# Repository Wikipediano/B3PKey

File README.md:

# B3PKey
 This is the first custom keyboard that I have designed.
 It is an ortholinear 75% keyboard which, when completed, will have been entirely designed and built by me.
 
 I have been inspired to do this project by <a href="https://www.reddit.com/user/JustOneMorePixel">u/JustOneMorePixel</a>, and I have gone through ai03's book <a href="https://wiki.ai03.com/books/pcb-design">*PCB Design*</a> and Hadi Iskandarani's YouTube series <a href="https://www.youtube.com/playlist?list=PLbtY7JsOJDYkHNuTmBtGgaWv_qipKeL-u">*PCB Design for Mechanical Keyboards*</a>.

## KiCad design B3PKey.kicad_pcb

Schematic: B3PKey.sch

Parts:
C1, C2: 22pF; C_0805_2012Metric
C3: 1uF; C_0805_2012Metric
C4, C5, C6: 0.1uF; C_0805_2012Metric
C7: 10uF; C_0805_2012Metric
D1, D2, D3, D4, D5, D6, D7, D8, D9, D10, D11, D12, D13, D14, D15, D16, D17, D18, D19, D20, D21, D22, D23, D24, D25, D26, D27, D28, D29, D30, D31, D32, D33, D34, D35, D36, D37, D38, D39, D40, D41, D42, D43, D44, D45, D46, D47, D48, D49, D50, D51, D52, D53, D54, D55, D56, D57, D58, D59, D60, D61, D62, D63, D64, D65, D66, D67, D68, D69, D70, D71, D72, D73, D74, D75, D76, D77, D78: D_Small; D_SOD-123
F1: 500mA; Fuse_0805_2012Metric
MX1, MX2, MX3, MX4, MX5, MX6, MX7, MX8, MX9, MX10, MX11, MX12, MX13, MX14, MX15, MX16, MX17, MX18, MX19, MX20, MX21, MX22, MX23, MX24, MX25, MX26, MX27, MX28, MX29, MX30, MX31, MX32, MX33, MX34, MX35, MX36, MX37, MX38, MX39, MX40, MX41, MX42, MX43, MX44, MX45, MX46, MX47, MX48, MX49, MX50, MX51, MX52, MX53, MX54, MX56, MX57, MX58, MX59, MX60, MX61, MX62, MX63, MX64, MX65, MX66, MX67, MX68, MX69, MX70, MX71, MX72, MX74, MX75, MX76, MX77, MX78: MX-NoLED; MXOnly-1U-NoLED
MX55: MX-NoLED; MXOnly-2U-NoLED
MX73: MX-NoLED; MXOnly-6U-ReversedStabilizers-NoLED
R1, R4: 10k; R_0805_2012Metric
R2, R3: 22; R_0805_2012Metric
R5, R6: 5.1k; R_0805_2012Metric
SW1: SW_Push; SKQG-1155865
U1: ATmega32U4-AU; TQFP-44_10x10mm_P0.8mm
USB1: HRO-TYPE-C-31-M-12; HRO-TYPE-C-31-M-12-HandSoldering
Y1: 16MHz; Crystal_SMD_3225-4Pin_3.2x2.5mm

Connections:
+5V: C4.1, C5.1, C6.1, C7.1, F1.1, R1.1, U1.2, U1.7, U1.14, U1.24, U1.34, U1.44
/CC1: R6.2, USB1.4
/CC2: R5.2, USB1.10
/D_N: R3.1, U1.3
/D_P: R2.1, U1.4
COL0: MX1.1 (COL), MX15.1 (COL), MX29.1 (COL), MX43.1 (COL), MX56.1 (COL), MX70.1 (COL), U1.26
COL1: MX2.1 (COL), MX16.1 (COL), MX30.1 (COL), MX44.1 (COL), MX57.1 (COL), MX71.1 (COL), U1.27
COL2: MX3.1 (COL), MX17.1 (COL), MX31.1 (COL), MX45.1 (COL), MX58.1 (COL), MX72.1 (COL), U1.28
COL3: MX4.1 (COL), MX18.1 (COL), MX32.1 (COL), MX46.1 (COL), MX59.1 (COL), U1.29
COL4: MX5.1 (COL), MX19.1 (COL), MX33.1 (COL), MX47.1 (COL), MX60.1 (COL), U1.30
COL5: MX6.1 (COL), MX20.1 (COL), MX34.1 (COL), MX48.1 (COL), MX61.1 (COL), U1.31
COL6: MX7.1 (COL), MX21.1 (COL), MX35.1 (COL), MX49.1 (COL), MX62.1 (COL), MX73.1 (COL), U1.32
COL7: MX8.1 (COL), MX22.1 (COL), MX36.1 (COL), MX50.1 (COL), MX63.1 (COL), U1.36
COL8: MX9.1 (COL), MX23.1 (COL), MX37.1 (COL), MX51.1 (COL), MX64.1 (COL), U1.1
COL9: MX10.1 (COL), MX24.1 (COL), MX38.1 (COL), MX52.1 (COL), MX65.1 (COL), MX74.1 (COL), U1.8
COL10: MX11.1 (COL), MX25.1 (COL), MX39.1 (COL), MX53.1 (COL), MX66.1 (COL), MX75.1 (COL), U1.9
COL11: MX12.1 (COL), MX26.1 (COL), MX40.1 (COL), MX54.1 (COL), MX67.1 (COL), MX76.1 (COL), U1.10
COL12: MX13.1 (COL), MX27.1 (COL), MX41.1 (COL), MX55.1 (COL), MX68.1 (COL), MX77.1 (COL), U1.11
COL13: MX14.1 (COL), MX28.1 (COL), MX42.1 (COL), MX69.1 (COL), MX78.1 (COL), U1.12
D+: R2.2, USB1.6, USB1.8
D-: R3.2, USB1.5, USB1.7
GND: C1.2, C2.2, C3.2, C4.2, C5.2, C6.2, C7.2, R4.1, R5.1, R6.1, SW1.1, U1.5, U1.15, U1.23, U1.35, U1.43, USB1.1, USB1.12, USB1.13, Y1.2, Y1.4
unnamed: C1.1, U1.17, Y1.1
unnamed: C2.1, U1.16, Y1.3
unnamed: C3.1, U1.6
unnamed: D1.2 (A), MX1.2 (ROW)
unnamed: D2.2 (A), MX2.2 (ROW)
unnamed: D3.2 (A), MX3.2 (ROW)
unnamed: D4.2 (A), MX4.2 (ROW)
unnamed: D5.2 (A), MX5.2 (ROW)
unnamed: D6.2 (A), MX6.2 (ROW)
unnamed: D7.2 (A), MX7.2 (ROW)
unnamed: D8.2 (A), MX8.2 (ROW)
unnamed: D9.2 (A), MX9.2 (ROW)
unnamed: D10.2 (A), MX10.2 (ROW)
unnamed: D11.2 (A), MX11.2 (ROW)
unnamed: D12.2 (A), MX12.2 (ROW)
unnamed: D13.2 (A), MX13.2 (ROW)
unnamed: D14.2 (A), MX14.2 (ROW)
unnamed: D15.2 (A), MX15.2 (ROW)
unnamed: D16.2 (A), MX16.2 (ROW)
unnamed: D17.2 (A), MX17.2 (ROW)
unnamed: D18.2 (A), MX18.2 (ROW)
unnamed: D19.2 (A), MX19.2 (ROW)
unnamed: D20.2 (A), MX20.2 (ROW)
unnamed: D21.2 (A), MX21.2 (ROW)
unnamed: D22.2 (A), MX22.2 (ROW)
unnamed: D23.2 (A), MX23.2 (ROW)
unnamed: D24.2 (A), MX24.2 (ROW)
unnamed: D25.2 (A), MX25.2 (ROW)
unnamed: D26.2 (A), MX26.2 (ROW)
unnamed: D27.2 (A), MX27.2 (ROW)
unnamed: D28.2 (A), MX28.2 (ROW)
unnamed: D29.2 (A), MX29.2 (ROW)
unnamed: D30.2 (A), MX30.2 (ROW)
unnamed: D31.2 (A), MX31.2 (ROW)
unnamed: D32.2 (A), MX32.2 (ROW)
unnamed: D33.2 (A), MX33.2 (ROW)
unnamed: D34.2 (A), MX34.2 (ROW)
unnamed: D35.2 (A), MX35.2 (ROW)
unnamed: D36.2 (A), MX36.2 (ROW)
unnamed: D37.2 (A), MX37.2 (ROW)
unnamed: D38.2 (A), MX38.2 (ROW)
unnamed: D39.2 (A), MX39.2 (ROW)
unnamed: D40.2 (A), MX40.2 (ROW)
unnamed: D41.2 (A), MX41.2 (ROW)
unnamed: D42.2 (A), MX42.2 (ROW)
unnamed: D43.2 (A), MX43.2 (ROW)
unnamed: D44.2 (A), MX44.2 (ROW)
unnamed: D45.2 (A), MX45.2 (ROW)
unnamed: D46.2 (A), MX46.2 (ROW)
unnamed: D47.2 (A), MX47.2 (ROW)
unnamed: D48.2 (A), MX48.2 (ROW)
unnamed: D49.2 (A), MX49.2 (ROW)
unnamed: D50.2 (A), MX50.2 (ROW)
unnamed: D51.2 (A), MX51.2 (ROW)
unnamed: D52.2 (A), MX52.2 (ROW)
unnamed: D53.2 (A), MX53.2 (ROW)
unnamed: D54.2 (A), MX54.2 (ROW)
unnamed: D55.2 (A), MX55.2 (ROW)
unnamed: D56.2 (A), MX56.2 (ROW)
unnamed: D57.2 (A), MX57.2 (ROW)
unnamed: D58.2 (A), MX58.2 (ROW)
unnamed: D59.2 (A), MX59.2 (ROW)
unnamed: D60.2 (A), MX60.2 (ROW)
unnamed: D61.2 (A), MX61.2 (ROW)
unnamed: D62.2 (A), MX62.2 (ROW)
unnamed: D63.2 (A), MX63.2 (ROW)
unnamed: D64.2 (A), MX64.2 (ROW)
unnamed: D65.2 (A), MX65.2 (ROW)
unnamed: D66.2 (A), MX66.2 (ROW)
unnamed: D67.2 (A), MX67.2 (ROW)
unnamed: D68.2 (A), MX68.2 (ROW)
unnamed: D69.2 (A), MX69.2 (ROW)
unnamed: D70.2 (A), MX70.2 (ROW)
unnamed: D71.2 (A), MX71.2 (ROW)
unnamed: D72.2 (A), MX72.2 (ROW)
unnamed: D73.2 (A), MX73.2 (ROW)
unnamed: D74.2 (A), MX74.2 (ROW)
unnamed: D75.2 (A), MX75.2 (ROW)
unnamed: D76.2 (A), MX76.2 (ROW)
unnamed: D77.2 (A), MX77.2 (ROW)
unnamed: D78.2 (A), MX78.2 (ROW)
unnamed: R1.2, SW1.2, U1.13
unnamed: R4.2, U1.33
ROW0: D1.1 (K), D2.1 (K), D3.1 (K), D4.1 (K), D5.1 (K), D6.1 (K), D7.1 (K), D8.1 (K), D9.1 (K), D10.1 (K), D11.1 (K), D12.1 (K), D13.1 (K), D14.1 (K), U1.37
ROW1: D15.1 (K), D16.1 (K), D17.1 (K), D18.1 (K), D19.1 (K), D20.1 (K), D21.1 (K), D22.1 (K), D23.1 (K), D24.1 (K), D25.1 (K), D26.1 (K), D27.1 (K), D28.1 (K), U1.38
ROW2: D29.1 (K), D30.1 (K), D31.1 (K), D32.1 (K), D33.1 (K), D34.1 (K), D35.1 (K), D36.1 (K), D37.1 (K), D38.1 (K), D39.1 (K), D40.1 (K), D41.1 (K), D42.1 (K), U1.39
ROW3: D43.1 (K), D44.1 (K), D45.1 (K), D46.1 (K), D47.1 (K), D48.1 (K), D49.1 (K), D50.1 (K), D51.1 (K), D52.1 (K), D53.1 (K), D54.1 (K), D55.1 (K), U1.40
ROW4: D56.1 (K), D57.1 (K), D58.1 (K), D59.1 (K), D60.1 (K), D61.1 (K), D62.1 (K), D63.1 (K), D64.1 (K), D65.1 (K), D66.1 (K), D67.1 (K), D68.1 (K), D69.1 (K), U1.41
ROW5: D70.1 (K), D71.1 (K), D72.1 (K), D73.1 (K), D74.1 (K), D75.1 (K), D76.1 (K), D77.1 (K), D78.1 (K), U1.25
VCC: F1.2, USB1.2, USB1.11

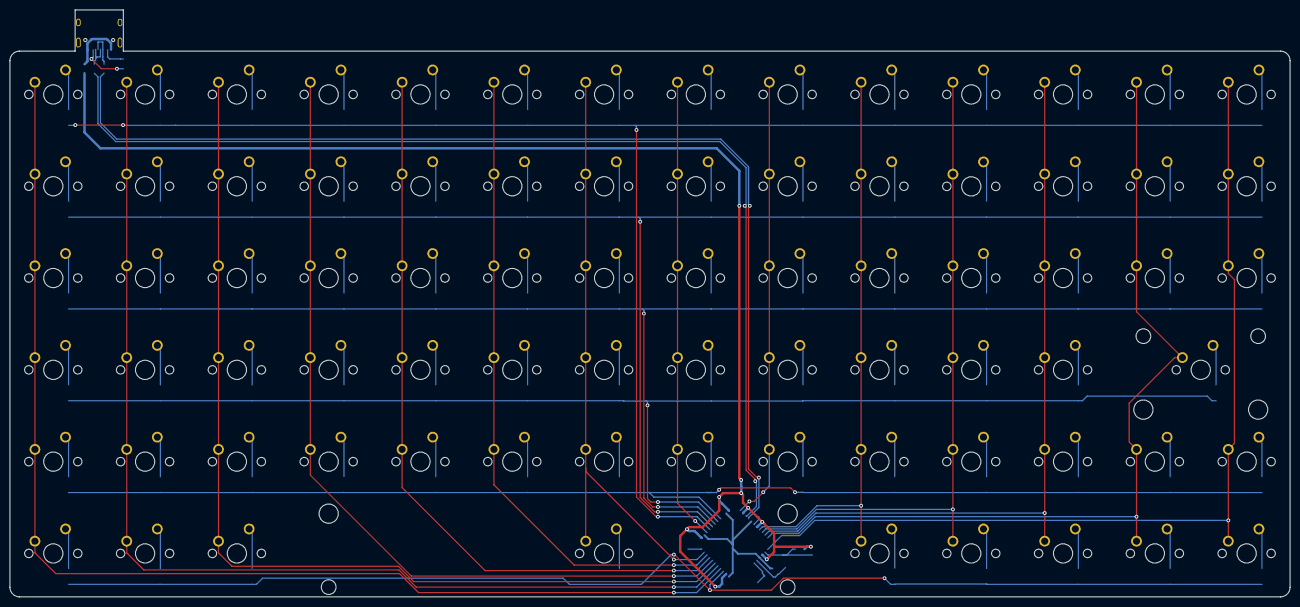
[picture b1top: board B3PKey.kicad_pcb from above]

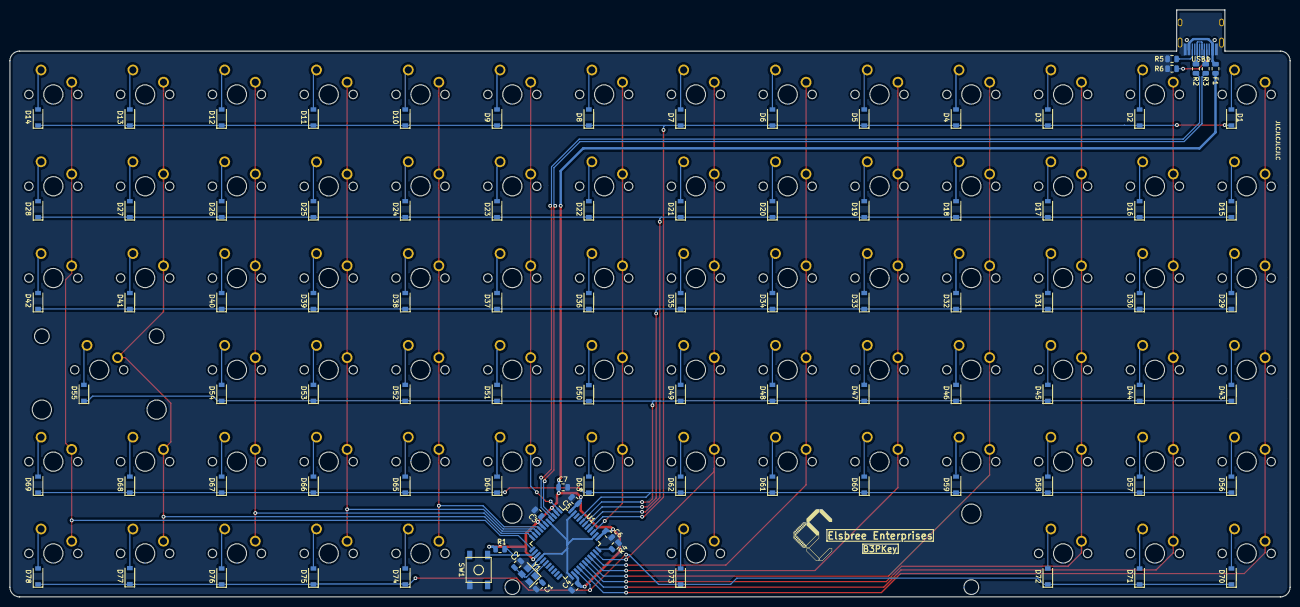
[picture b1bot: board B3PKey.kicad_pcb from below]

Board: 2 copper layers, 265.7 x 121.8 mm, 174 parts (96 on the bottom side), 112 nets.

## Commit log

2020-08-07 Add submodules
2020-08-07 Add libraries
2020-08-07 Controller and keyswitch schematic
2020-08-08 Updated switch matrix
2020-08-08 Keyswitch layout w/ diodes
2020-08-08 Flip spacebar stabs
2020-08-09 Matrix traces laid
2020-08-09 Matrix traces tweak
2020-08-10 Add submodule
2020-08-10 Add Elite-C footprint
2020-08-10 Update layout and replace microcontroller
2020-08-11 Modify silkscreen
2020-08-11 Update layout
2020-08-11 Add border and reference files
2020-08-11 Add edge cuts and place some components
2020-08-11 Route USB traces
2020-08-13 Some routing
2020-08-13 Route more traces
2020-08-14 Move components to forehead and route all traces
2020-08-14 Update placement and add edge cuts
2020-08-15 Rotate controller and reroute traces
2020-08-15 Change to USB Type-C
    Changed the board to use a USB Type-C connector, added required components and modified ground plane to be neater. Also generated OUTDATED Gerber files.
    TODO: Generate new Gerbers
2020-08-15 Update traces and gerbers
2020-08-15 Add some art
2020-08-18 Move components to spacebar
2020-08-22 Update Gerbers
2020-08-24 Add silkscreen logo, update gerbers
2020-08-24 Update silkscreen
2020-09-01 Update pbc outline, small tweaks
    Also generate new gerbers and add case_open dxf file
2020-09-01 Update gerbers and outline
